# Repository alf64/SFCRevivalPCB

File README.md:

# SFCRevivalPCB
PCBs for SFCRevival

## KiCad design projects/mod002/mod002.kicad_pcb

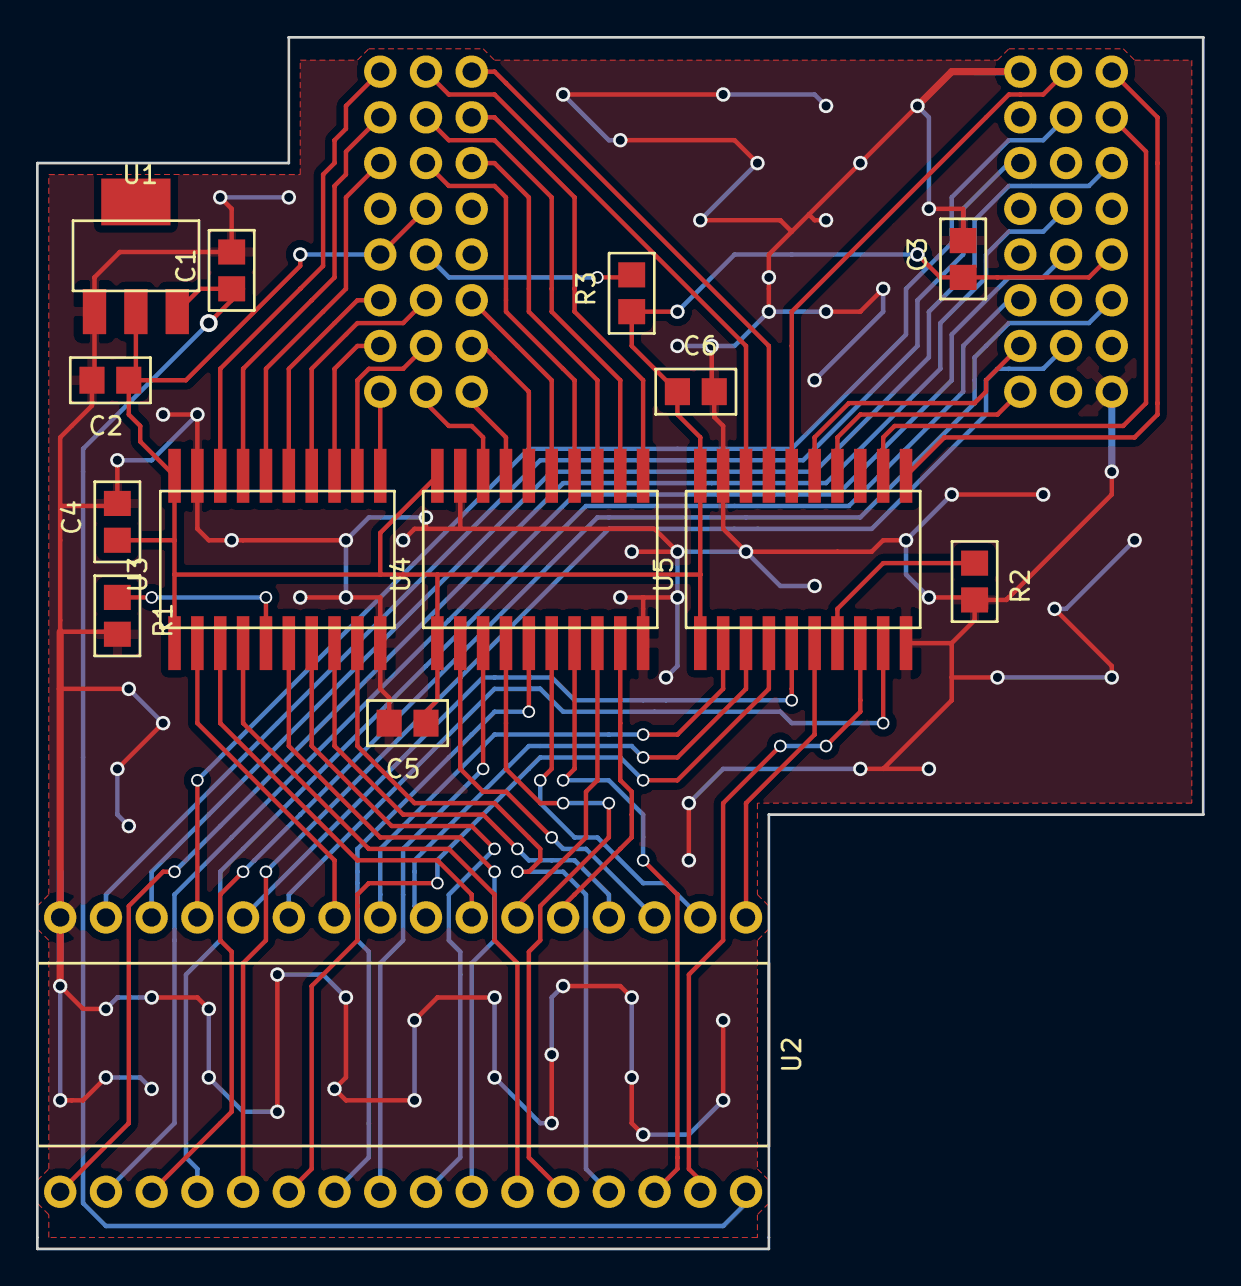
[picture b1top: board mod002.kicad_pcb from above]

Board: 2 copper layers, 64.8 x 67.3 mm, 15 parts (1 on the bottom side), 59 nets.

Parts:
C1, C2, C3, C4, C5, C6: 100n; 0805
R1, R2, R3: 0; 0805
U1: LD1117S33TR; SOT223
U2: SFC_MaskRom_32pin_SOCKET; PDIP32
U3, U4, U5: 74LVC245; SO20
U6: SST39VF1681_1682; GOTRONIK_ADAP_TSOP48

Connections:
+3V3_: C2.1, C3.1, C4.1, C5.1, C6.1, R3.1, U1.2, U3.1, U3.20, U4.1, U4.20, U5.1, U5.20, U6.12, U6.14, U6.37
/A0_3V: U5.15, U6.45
/A0_5V: U2.12, U5.5
/A1_3V: U5.11, U6.25
/A1_5V: U2.11, U5.9
/A2_3V: U3.18, U6.24
/A2_5V: U2.10, U3.2
/A3_3V: U5.18, U6.23
/A3_5V: U2.9, U5.2
/A4_3V: U5.17, U6.22
/A4_5V: U2.8, U5.3
/A5_3V: U3.17, U6.21
/A5_5V: U2.7, U3.3
/A6_3V: U4.12, U6.20
/A6_5V: U2.6, U4.8
/A7_3V: U4.11, U6.19
/A7_5V: U2.5, U4.9
/A8_3V: U3.16, U6.18
/A8_5V: U2.27, U3.4
/A9_3V: U3.14, U6.8
/A9_5V: U2.26, U3.6
/A10_3V: U4.15, U6.7
/A10_5V: U2.23, U4.5
/A11_3V: U3.13, U6.6
/A11_5V: U2.25, U3.7
/A12_3V: U3.12, U6.5
/A12_5V: U2.4, U3.8
/A13_3V: U4.16, U6.4
/A13_5V: U2.28, U4.4
/A14_3V: U3.11, U6.3
/A14_5V: U2.29, U3.9
/A15_3V: U4.18, U6.2
/A15_5V: U2.3, U4.2
/A16_3V: U4.17, U6.1
/A16_5V: U2.24, U4.3
/A17_3V: U5.14, U6.48
/A17_5V: U2.1, U5.6
/A18_3V: U4.14, U6.17
/A18_5V: U2.2, U4.6
/A19_3V: U4.13, U6.16
/A19_5V: U2.30, U4.7
/A20_3V: U3.15, U6.9
/D0_3V: U2.13, U6.29
/D1_3V: U2.14, U6.31
/D2_3V: U2.15, U6.33
/D3_3V: U2.17, U6.35
/D4_3V: U2.18, U6.38
/D5_3V: U2.19, U6.40
/D6_3V: U2.20, U6.42
/D7_3V: U2.21, U6.44
/FLASH_CE: U5.16, U6.26
/FLASH_OE: U5.12, U6.28
/ROM_CE: U2.22, U5.4
/ROM_OE: U2.31, U5.8
GND_: C1.2, C2.2, C3.2, C4.2, C5.2, C6.2, R1.2, R2.2, U1.1, U2.16, U3.10, U3.19, U4.10, U4.19, U5.10, U5.19, U6.27, U6.46
unnamed: R1.1, U3.5
unnamed: R2.1, U5.7
unnamed: R3.2, U6.11
VCC_: C1.1, U1.3, U2.32

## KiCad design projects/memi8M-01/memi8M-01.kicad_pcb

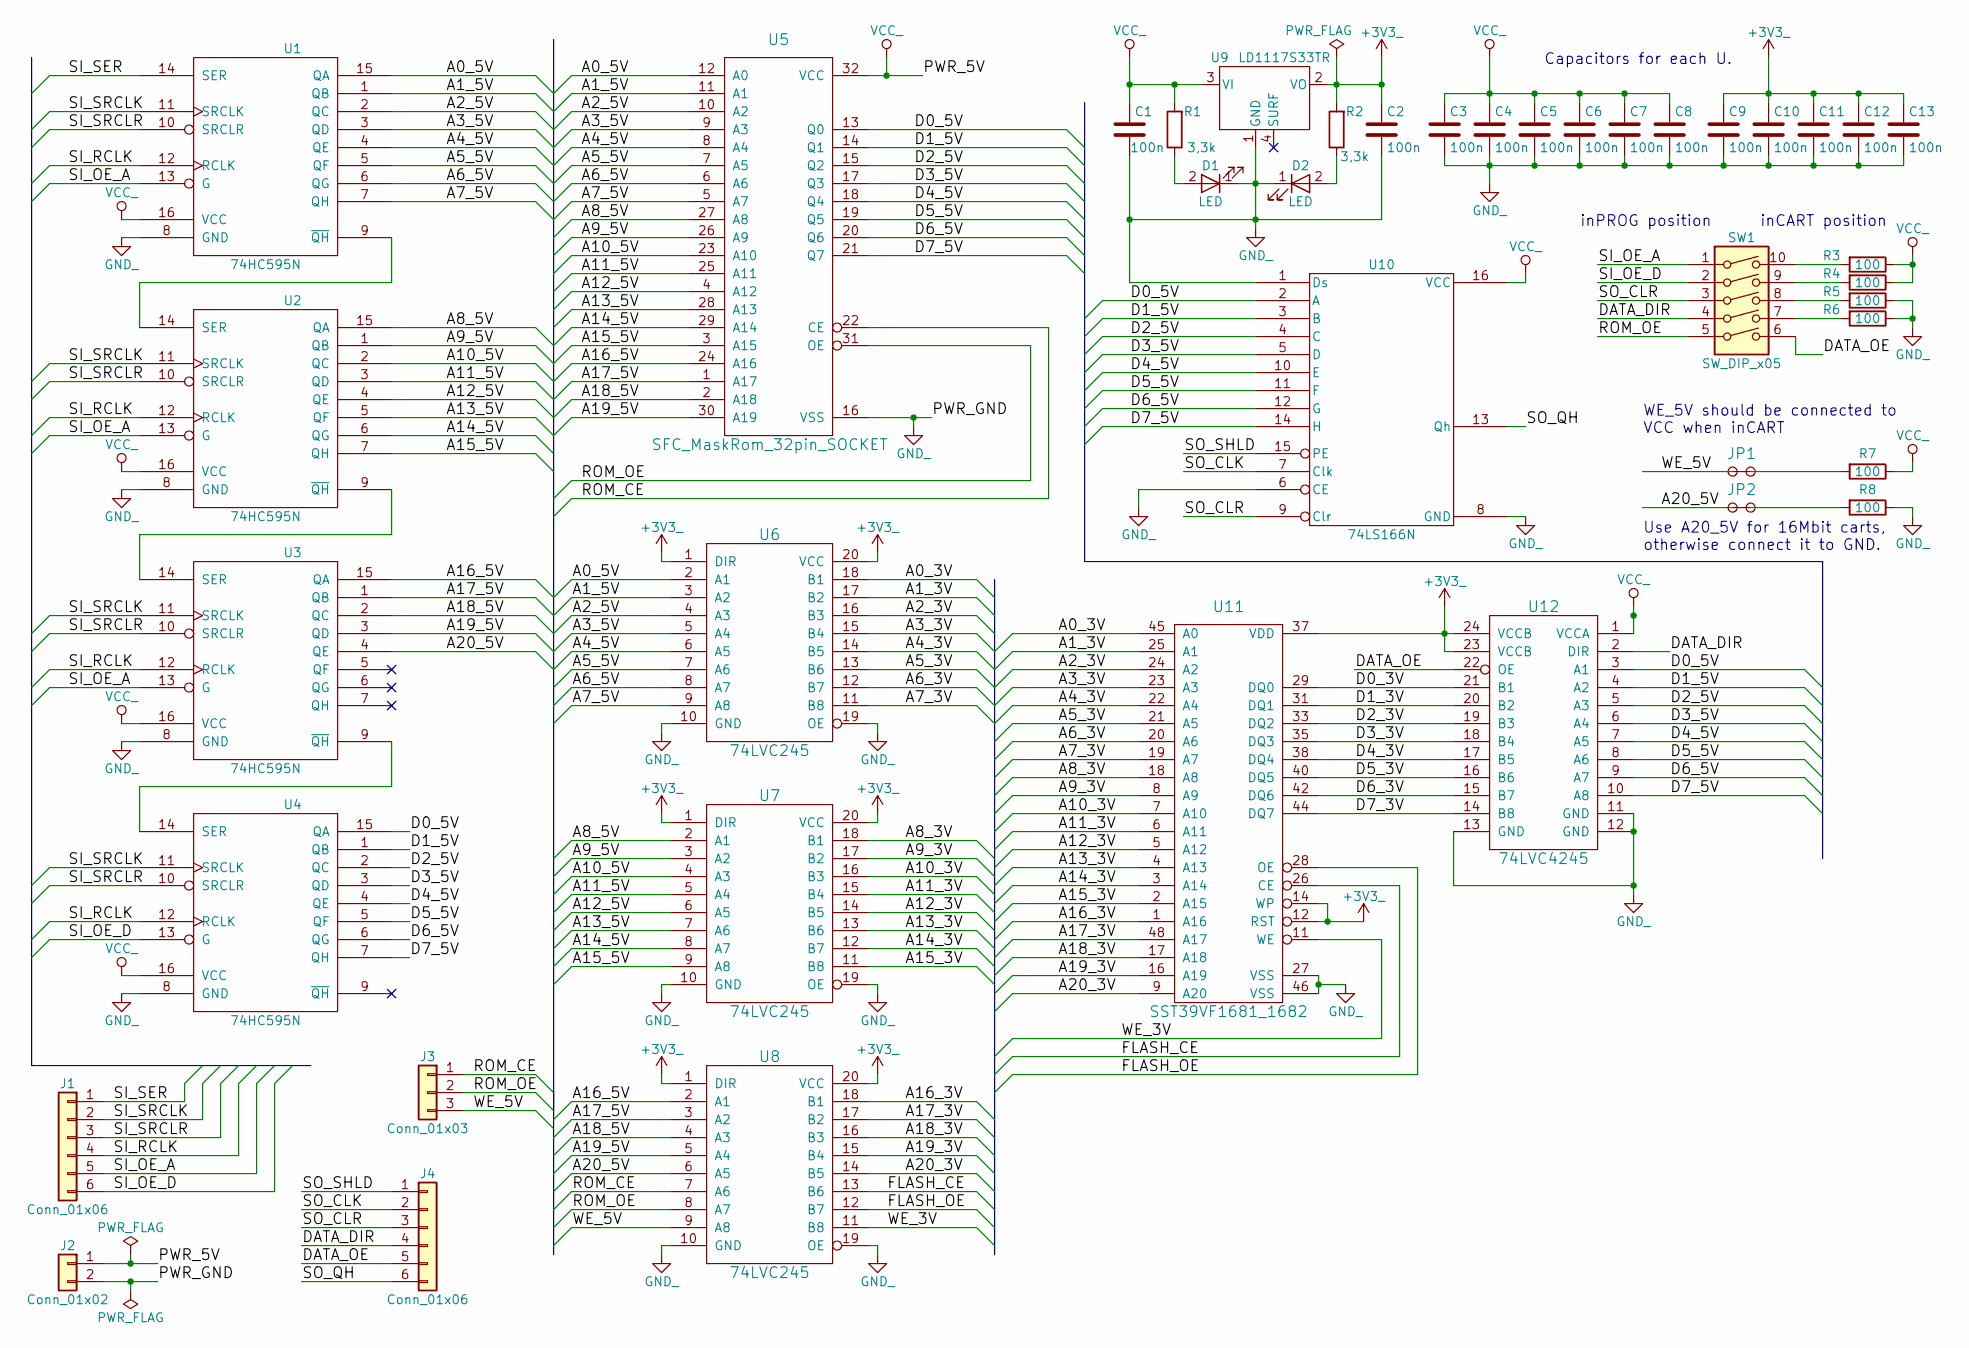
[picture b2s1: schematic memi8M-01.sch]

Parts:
C1, C2, C3, C4, C5, C6, C7, C8, C9, C10, C11, C12, C13: 100n; 0805
D1, D2: LED; 0805
J1, J4: Conn_01x06; PINHEAD1x6
J2: Conn_01x02; PINHEAD1x2
J3: Conn_01x03; PINHEAD1x3
JP1, JP2: SINGLE_JUMPER; PINHEAD1x2
R1, R2: 3,3k; 0805
R3, R4, R5, R6, R7, R8: 100; 0805
SW1: SW_DIP_x05
U1, U2, U3, U4: 74HC595N; SO16
U5: SFC_MaskRom_32pin_SOCKET; PDIP32
U6, U7, U8: 74LVC245; SO20
U9: LD1117S33TR; SOT223
U10: 74LS166N; SO16
U11: SST39VF1681_1682; GOTRONIK_ADAP_TSOP48
U12: 74LVC4245; SO24

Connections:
+3V3_: C2.1, C9.1, C10.1, C11.1, C12.1, C13.1, R2.2, U6.1 (DIR), U6.20 (VCC), U7.1 (DIR), U7.20 (VCC), U8.1 (DIR), U8.20 (VCC), U9.2 (VO), U11.12 (RST), U11.14 (WP), U11.37 (VDD), U12.23 (VCCB), U12.24 (VCCB)
/A0_3V: U6.18 (B1), U11.45 (A0)
/A0_5V: U1.15 (QA), U5.12 (A0), U6.2 (A1)
/A1_3V: U6.17 (B2), U11.25 (A1)
/A1_5V: U1.1 (QB), U5.11 (A1), U6.3 (A2)
/A2_3V: U6.16 (B3), U11.24 (A2)
/A2_5V: U1.2 (QC), U5.10 (A2), U6.4 (A3)
/A3_3V: U6.15 (B4), U11.23 (A3)
/A3_5V: U1.3 (QD), U5.9 (A3), U6.5 (A4)
/A4_3V: U6.14 (B5), U11.22 (A4)
/A4_5V: U1.4 (QE), U5.8 (A4), U6.6 (A5)
/A5_3V: U6.13 (B6), U11.21 (A5)
/A5_5V: U1.5 (QF), U5.7 (A5), U6.7 (A6)
/A6_3V: U6.12 (B7), U11.20 (A6)
/A6_5V: U1.6 (QG), U5.6 (A6), U6.8 (A7)
/A7_3V: U6.11 (B8), U11.19 (A7)
/A7_5V: U1.7 (QH), U5.5 (A7), U6.9 (A8)
/A8_3V: U7.18 (B1), U11.18 (A8)
/A8_5V: U2.15 (QA), U5.27 (A8), U7.2 (A1)
/A9_3V: U7.17 (B2), U11.8 (A9)
/A9_5V: U2.1 (QB), U5.26 (A9), U7.3 (A2)
/A10_3V: U7.16 (B3), U11.7 (A10)
/A10_5V: U2.2 (QC), U5.23 (A10), U7.4 (A3)
/A11_3V: U7.15 (B4), U11.6 (A11)
/A11_5V: U2.3 (QD), U5.25 (A11), U7.5 (A4)
/A12_3V: U7.14 (B5), U11.5 (A12)
/A12_5V: U2.4 (QE), U5.4 (A12), U7.6 (A5)
/A13_3V: U7.13 (B6), U11.4 (A13)
/A13_5V: U2.5 (QF), U5.28 (A13), U7.7 (A6)
/A14_3V: U7.12 (B7), U11.3 (A14)
/A14_5V: U2.6 (QG), U5.29 (A14), U7.8 (A7)
/A15_3V: U7.11 (B8), U11.2 (A15)
/A15_5V: U2.7 (QH), U5.3 (A15), U7.9 (A8)
/A16_3V: U8.18 (B1), U11.1 (A16)
/A16_5V: U3.15 (QA), U5.24 (A16), U8.2 (A1)
/A17_3V: U8.17 (B2), U11.48 (A17)
/A17_5V: U3.1 (QB), U5.1 (A17), U8.3 (A2)
/A18_3V: U8.16 (B3), U11.17 (A18)
/A18_5V: U3.2 (QC), U5.2 (A18), U8.4 (A3)
/A19_3V: U8.15 (B4), U11.16 (A19)
/A19_5V: U3.3 (QD), U5.30 (A19), U8.5 (A4)
/A20_3V: U8.14 (B5), U11.9 (A20)
/A20_5V: JP2.1 (A), U3.4 (QE), U8.6 (A5)
/D0_3V: U11.29 (DQ0), U12.21 (B1)
/D0_5V: U4.15 (QA), U5.13 (Q0), U10.2 (A), U12.3 (A1)
/D1_3V: U11.31 (DQ1), U12.20 (B2)
/D1_5V: U4.1 (QB), U5.14 (Q1), U10.3 (B), U12.4 (A2)
/D2_3V: U11.33 (DQ2), U12.19 (B3)
/D2_5V: U4.2 (QC), U5.15 (Q2), U10.4 (C), U12.5 (A3)
/D3_3V: U11.35 (DQ3), U12.18 (B4)
/D3_5V: U4.3 (QD), U5.17 (Q3), U10.5 (D), U12.6 (A4)
/D4_3V: U11.38 (DQ4), U12.17 (B5)
/D4_5V: U4.4 (QE), U5.18 (Q4), U10.10 (E), U12.7 (A5)
/D5_3V: U11.40 (DQ5), U12.16 (B6)
/D5_5V: U4.5 (QF), U5.19 (Q5), U10.11 (F), U12.8 (A6)
/D6_3V: U11.42 (DQ6), U12.15 (B7)
/D6_5V: U4.6 (QG), U5.20 (Q6), U10.12 (G), U12.9 (A7)
/D7_3V: U11.44 (DQ7), U12.14 (B8)
/D7_5V: U4.7 (QH), U5.21 (Q7), U10.14 (H), U12.10 (A8)
/DATA_DIR: J4.4, SW1.4, U12.2 (DIR)
/DATA_OE: J4.5, SW1.6, U12.22 (OE)
/FLASH_CE: U8.13 (B6), U11.26 (CE)
/FLASH_OE: U8.12 (B7), U11.28 (OE)
/ROM_CE: J3.1, U5.22 (CE), U8.7 (A6)
/ROM_OE: J3.2, SW1.5, U5.31 (OE), U8.8 (A7)
/SI_OE_A: J1.5, SW1.1, U1.13 (G), U2.13 (G), U3.13 (G)
/SI_OE_D: J1.6, SW1.2, U4.13 (G)
/SI_RCLK: J1.4, U1.12 (RCLK), U2.12 (RCLK), U3.12 (RCLK), U4.12 (RCLK)
/SI_SER: J1.1, U1.14 (SER)
/SI_SRCLK: J1.2, U1.11 (SRCLK), U2.11 (SRCLK), U3.11 (SRCLK), U4.11 (SRCLK)
/SI_SRCLR: J1.3, U1.10 (SRCLR), U2.10 (SRCLR), U3.10 (SRCLR), U4.10 (SRCLR)
/SO_CLK: J4.2, U10.7 (Clk)
/SO_CLR: J4.3, SW1.3, U10.9 (Clr)
/SO_QH: J4.6, U10.13 (Qh)
/SO_SHLD: J4.1, U10.15 (PE)
/WE_3V: U8.11 (B8), U11.11 (WE)
/WE_5V: J3.3, JP1.1 (A), U8.9 (A8)
GND_: C1.2, C2.2, C3.2, C4.2, C5.2, C6.2, C7.2, C8.2, C9.2, C10.2, C11.2, C12.2, C13.2, D1.1 (K), D2.1 (K), J2.2, R5.1, R6.1, R8.1, U1.8 (GND), U2.8 (GND), U3.8 (GND), U4.8 (GND), U5.16 (VSS), U6.10 (GND), U6.19 (OE), U7.10 (GND), U7.19 (OE), U8.10 (GND), U8.19 (OE), U9.1 (GND), U10.1 (Ds), U10.6 (CE), U10.8 (GND), U11.27 (VSS), U11.46 (VSS), U12.11 (GND), U12.12 (GND), U12.13 (GND)
unnamed: D1.2 (A), R1.1
unnamed: D2.2 (A), R2.1
unnamed: JP1.2 (B), R7.2
unnamed: JP2.2 (B), R8.2
unnamed: R3.2, SW1.10
unnamed: R4.2, SW1.9
unnamed: R5.2, SW1.8
unnamed: R6.2, SW1.7
unnamed: U1.9 (~QH), U2.14 (SER)
unnamed: U2.9 (~QH), U3.14 (SER)
unnamed: U3.9 (~QH), U4.14 (SER)
VCC_: C1.1, C3.1, C4.1, C5.1, C6.1, C7.1, C8.1, J2.1, R1.2, R3.1, R4.1, R7.1, U1.16 (VCC), U2.16 (VCC), U3.16 (VCC), U4.16 (VCC), U5.32 (VCC), U9.3 (VI), U10.16 (VCC), U12.1 (VCCA)

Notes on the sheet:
inCART position
Capacitors for each U.
inPROG position
Use A20_5V for 16Mbit carts, otherwise connect it to GND.
WE_5V should be connected to VCC when inCART

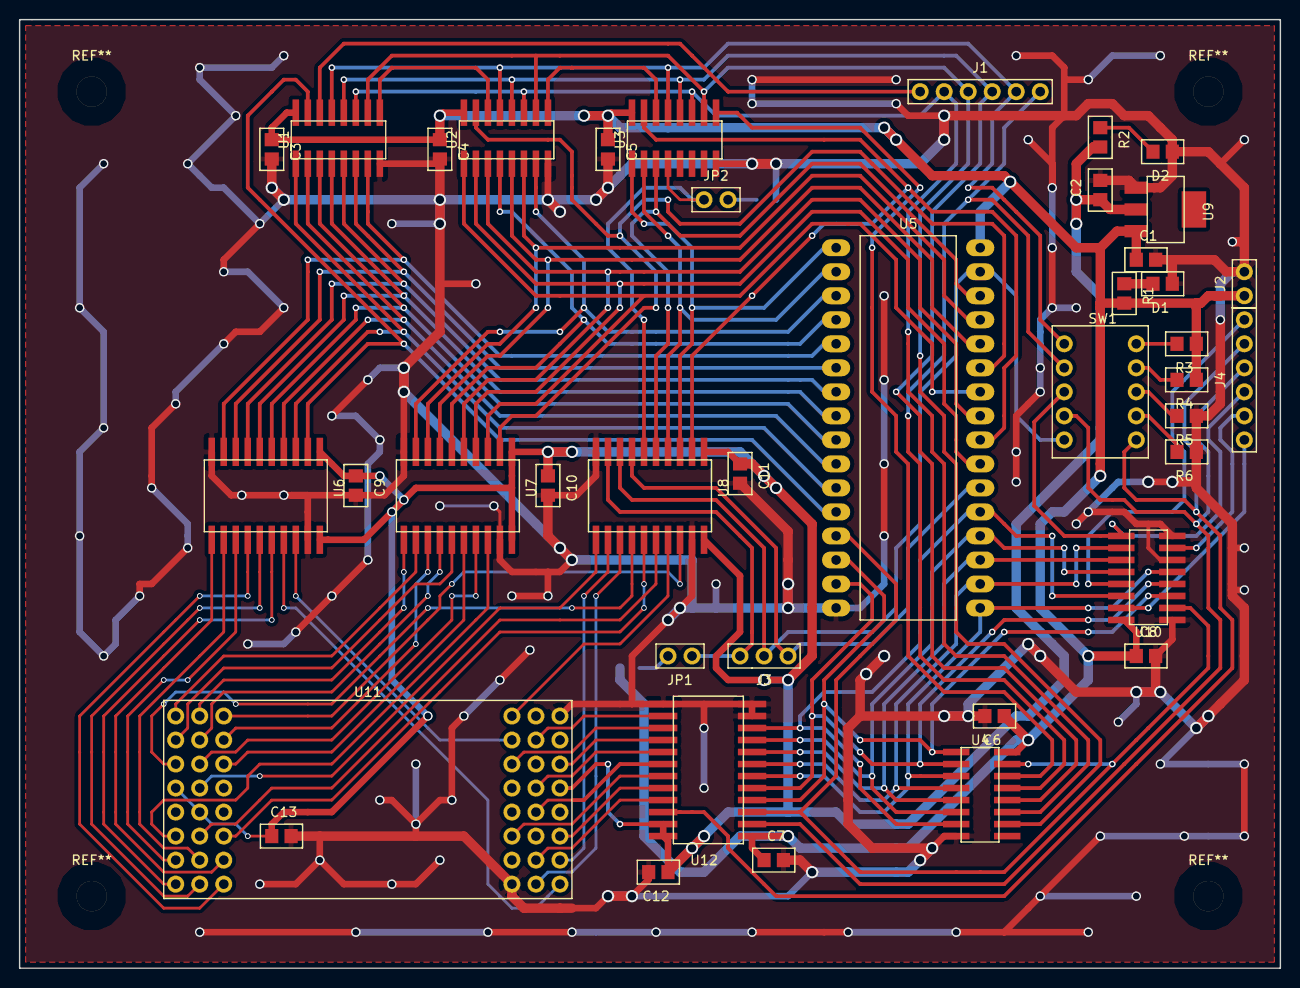
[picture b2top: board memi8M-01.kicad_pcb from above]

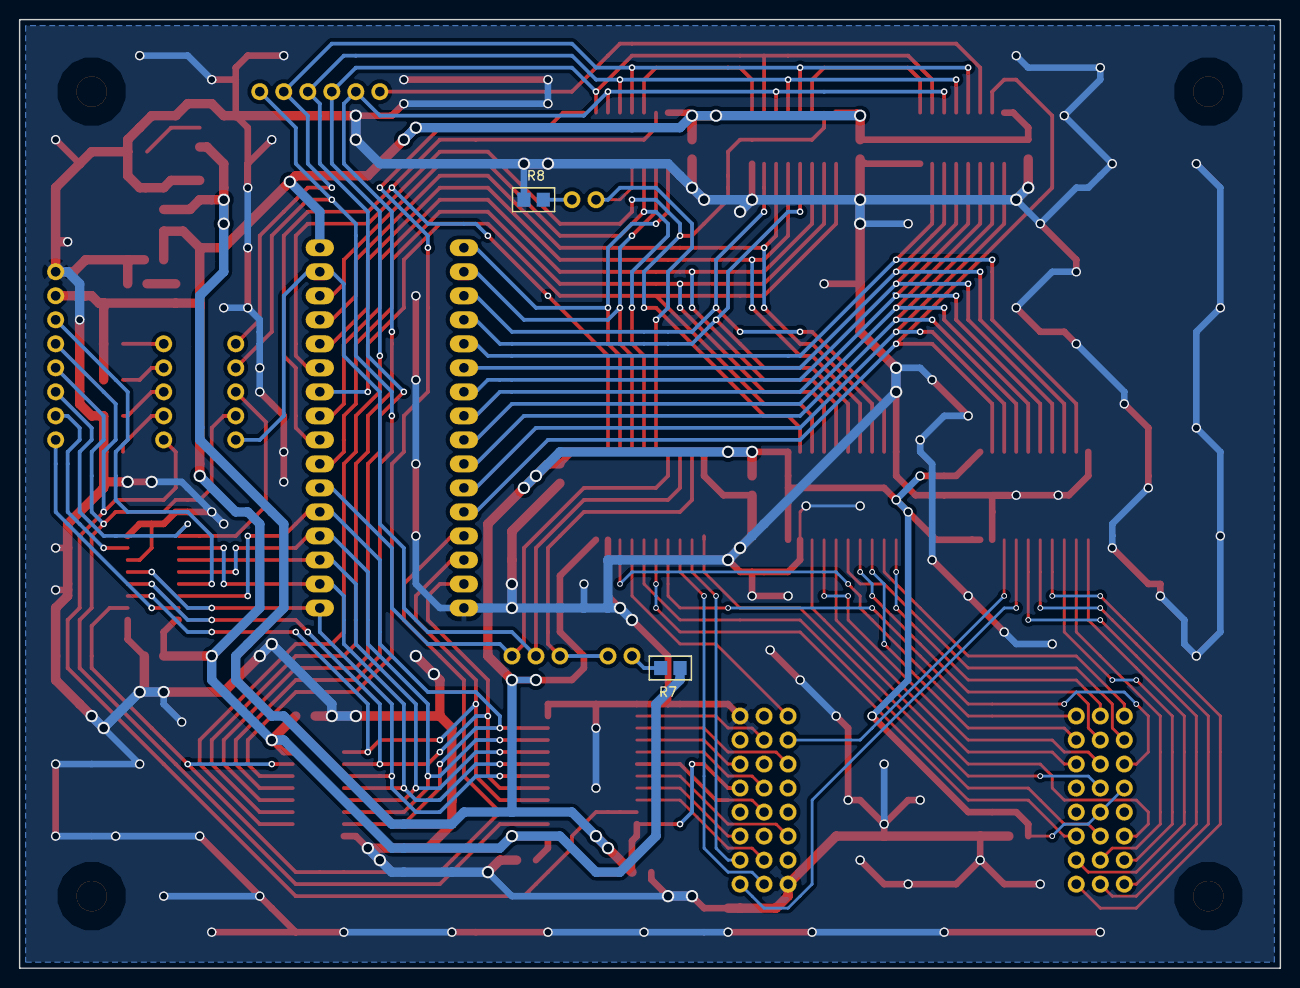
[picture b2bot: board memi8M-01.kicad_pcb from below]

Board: 2 copper layers, 133.4 x 100.3 mm, 42 parts (2 on the bottom side), 90 nets.

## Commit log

2018-12-10 Added .gitignore file.
2018-12-10 Initial commit with prototype projects.
2019-01-07 Added SO24 module package. Added memi8M (memory interface 8 Mbit) project.
2019-01-20 Added memi8M project. Added few mods (layouts) into alf64 mods library.
2019-01-25 1. memi8M project update. 2. New mods added.
2019-01-31 1. Sch of memi8M completed. 2. New lib elements and improvements. 3. BOM generated.
2019-02-02 Added so16 package layout.
2019-02-03 Update for modules, on the basis of real prototype PCBs patterns.
2019-02-10 Added dip switch x05, adjusted pdip16 holes.
2019-02-11 Added PDIP32 package and PINHEAD1x16. Added keywords to all packages. Added LDO 3.3V to lib, with 4 pins (4th is the surface to match package).
2019-02-11 Some module renamed for better overall accessibility. BOM updated. .net created. Modules associated to .net and schema.
2019-02-18 PCB design for memi8M halfway through.
2019-02-19 memi8M pcb update
2019-02-21 memi8M pcb update vol. 2
2019-02-22 memi8M pcb update vol. 3
2019-02-25 memi8M pcb update vol. 4
2019-02-26 memi8M pcb update vol. 5 - all connections done
2019-03-19 memi8M pcb update vol. 6 - pcb filled with copper
2019-03-20 Added mount holes.
2019-03-21 memi8M pcb update vol. 7 - ready for gerber creation
2019-03-21 memi8M PCB update vol. 8 - gerber files ready
2019-03-22 Added info.txt to memi8M pcb gerbers.
2020-01-16 Added mod001 and memi8M-01 projects.
2020-01-31 Prepared memi8M-01 for production. (Small fixes applied)
2020-01-31 Fixed mod001 (making pin 4 of U1 unconnected).
2020-02-11 Added mod002 project.
